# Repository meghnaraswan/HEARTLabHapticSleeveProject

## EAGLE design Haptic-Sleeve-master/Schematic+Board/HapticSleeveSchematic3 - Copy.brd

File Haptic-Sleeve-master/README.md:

# Haptic-Sleeve
Repository for the code used for the Haptic Sleeve Project!

Below is a brief description of the folders.

### CaseModels
Contains the 3D models that house the Haptic Sleeve PCB.

### ESP32 Code
Contains the Micropython code to run on the ESP32, along with Micropython firmware to flash (.bin file).

### Haptic Sleeve Testing Program
Contains the testing program and documentation for testing the Haptic Sleeve. The data extraction program (to convert log file data to CSV) also lives here.

### Learn To Write Code
Contains the code for the Learn To Write Software.

### Schematic+Board
Contains the schematic and board layout files for the Haptic Sleeve.

#### Activate venv
. venv/Scripts/activate

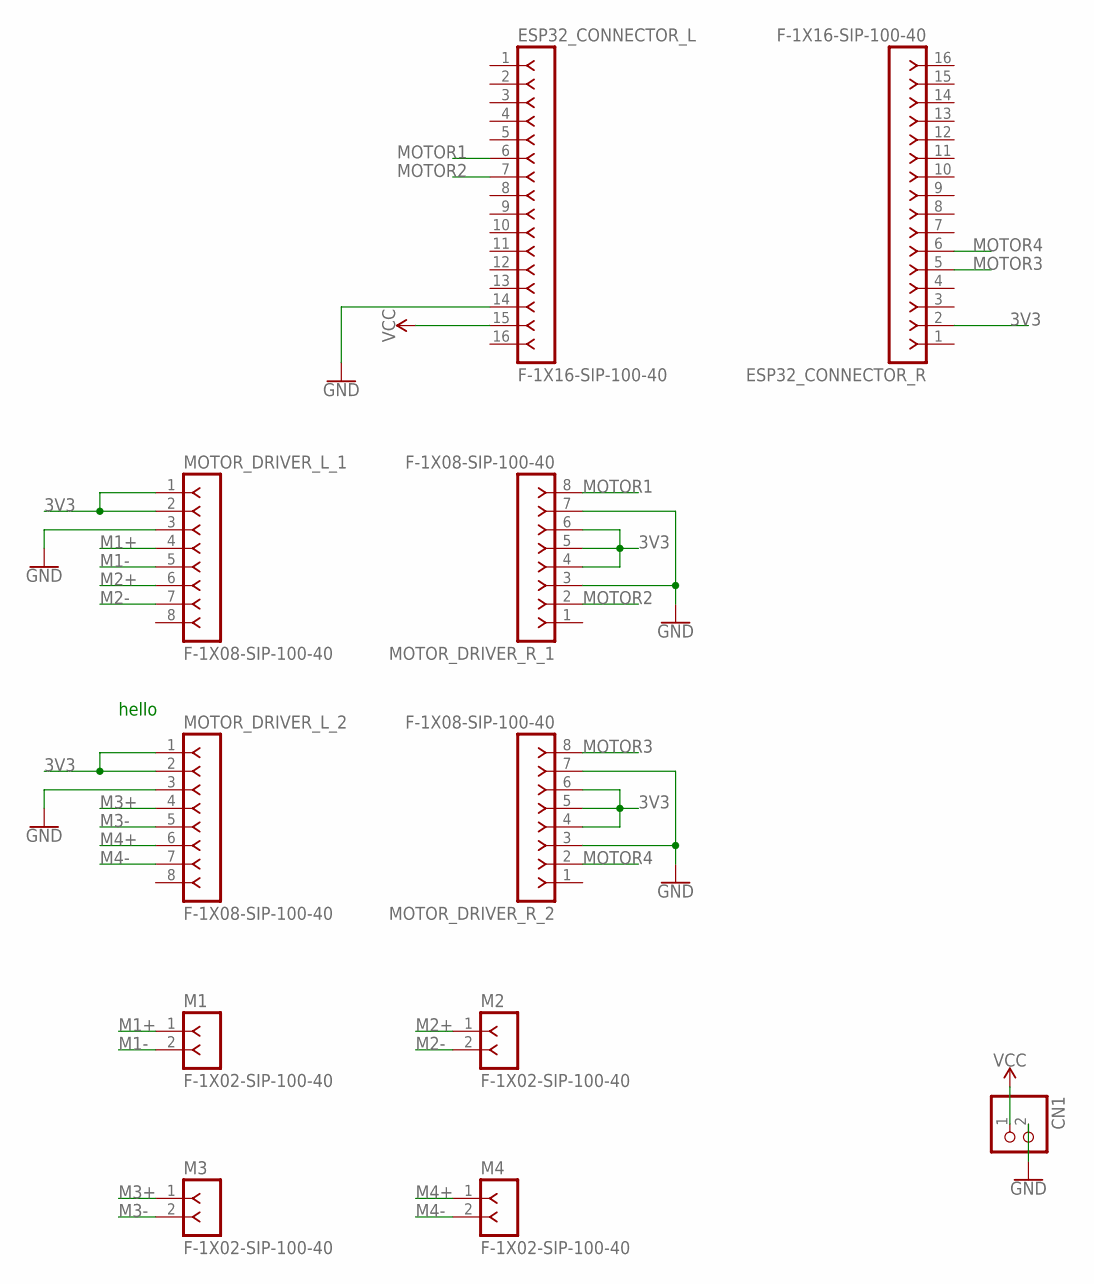
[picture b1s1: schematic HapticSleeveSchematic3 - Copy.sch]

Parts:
CN1: JST_2PIN-THM-RA; JST-PH-2-THM-RA
ESP32_CONNECTOR_L, ESP32_CONNECTOR_R: F-1X16-SIP-100-40; SIP-100-16-40
M1, M2, M3, M4: F-1X02-SIP-100-40; SIP-100-02-40
MOTOR_DRIVER_L_1, MOTOR_DRIVER_L_2: F-1X08-SIP-100-40; SIP-100-08-40
MOTOR_DRIVER_R_1, MOTOR_DRIVER_R_2: F-1X08-SIP-100-40; SIP-100-08-40

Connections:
3V3: ESP32_CONNECTOR_R.2, MOTOR_DRIVER_L_1.1, MOTOR_DRIVER_L_1.2, MOTOR_DRIVER_L_2.1, MOTOR_DRIVER_L_2.2, MOTOR_DRIVER_R_1.4, MOTOR_DRIVER_R_1.5, MOTOR_DRIVER_R_1.6, MOTOR_DRIVER_R_2.4, MOTOR_DRIVER_R_2.5, MOTOR_DRIVER_R_2.6
GND: CN1.2 (1), ESP32_CONNECTOR_L.14, MOTOR_DRIVER_L_1.3, MOTOR_DRIVER_L_2.3, MOTOR_DRIVER_R_1.3, MOTOR_DRIVER_R_1.7, MOTOR_DRIVER_R_2.3, MOTOR_DRIVER_R_2.7
M1+: M1.1, MOTOR_DRIVER_L_1.4
M1-: M1.2, MOTOR_DRIVER_L_1.5
M2+: M2.1, MOTOR_DRIVER_L_1.6
M2-: M2.2, MOTOR_DRIVER_L_1.7
M3+: M3.1, MOTOR_DRIVER_L_2.4
M3-: M3.2, MOTOR_DRIVER_L_2.5
M4+: M4.1, MOTOR_DRIVER_L_2.6
M4-: M4.2, MOTOR_DRIVER_L_2.7
MOTOR1: ESP32_CONNECTOR_L.6, MOTOR_DRIVER_R_1.8
MOTOR2: ESP32_CONNECTOR_L.7, MOTOR_DRIVER_R_1.2
MOTOR3: ESP32_CONNECTOR_R.5, MOTOR_DRIVER_R_2.8
MOTOR4: ESP32_CONNECTOR_R.6, MOTOR_DRIVER_R_2.2
VCC: CN1.1 (2), ESP32_CONNECTOR_L.15

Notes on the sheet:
hello

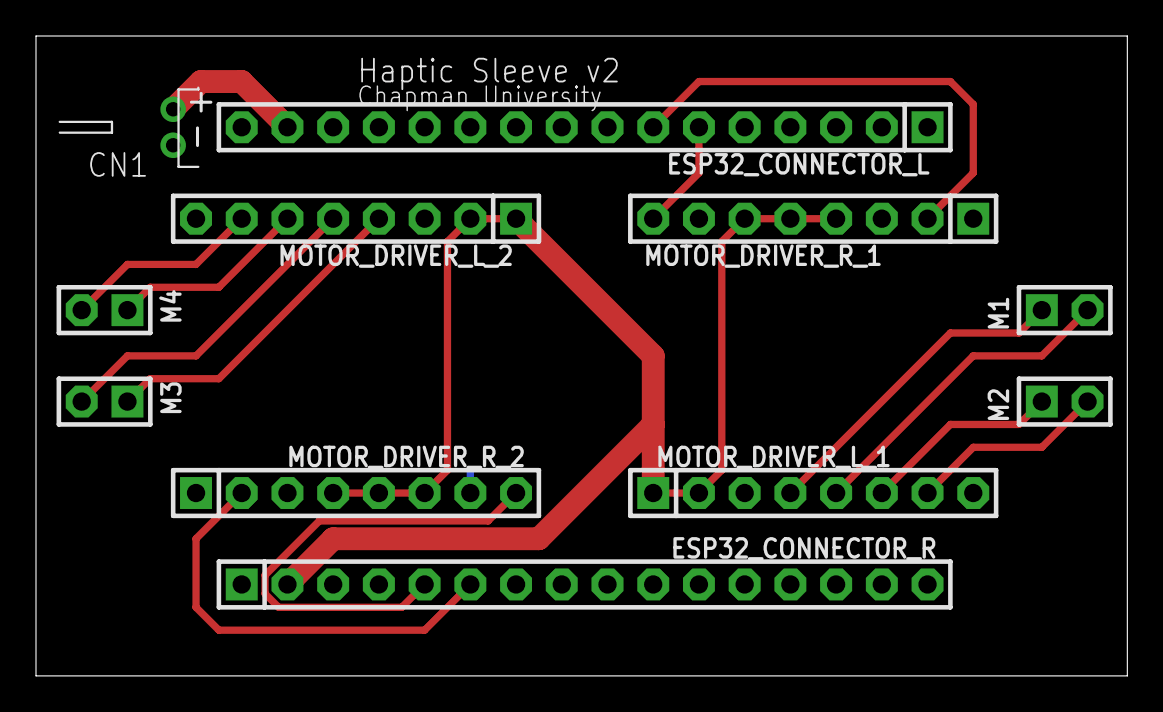
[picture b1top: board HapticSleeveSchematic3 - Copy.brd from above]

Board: 2 copper layers, 60.6 x 35.5 mm, 11 parts (0 on the bottom side), 15 nets.

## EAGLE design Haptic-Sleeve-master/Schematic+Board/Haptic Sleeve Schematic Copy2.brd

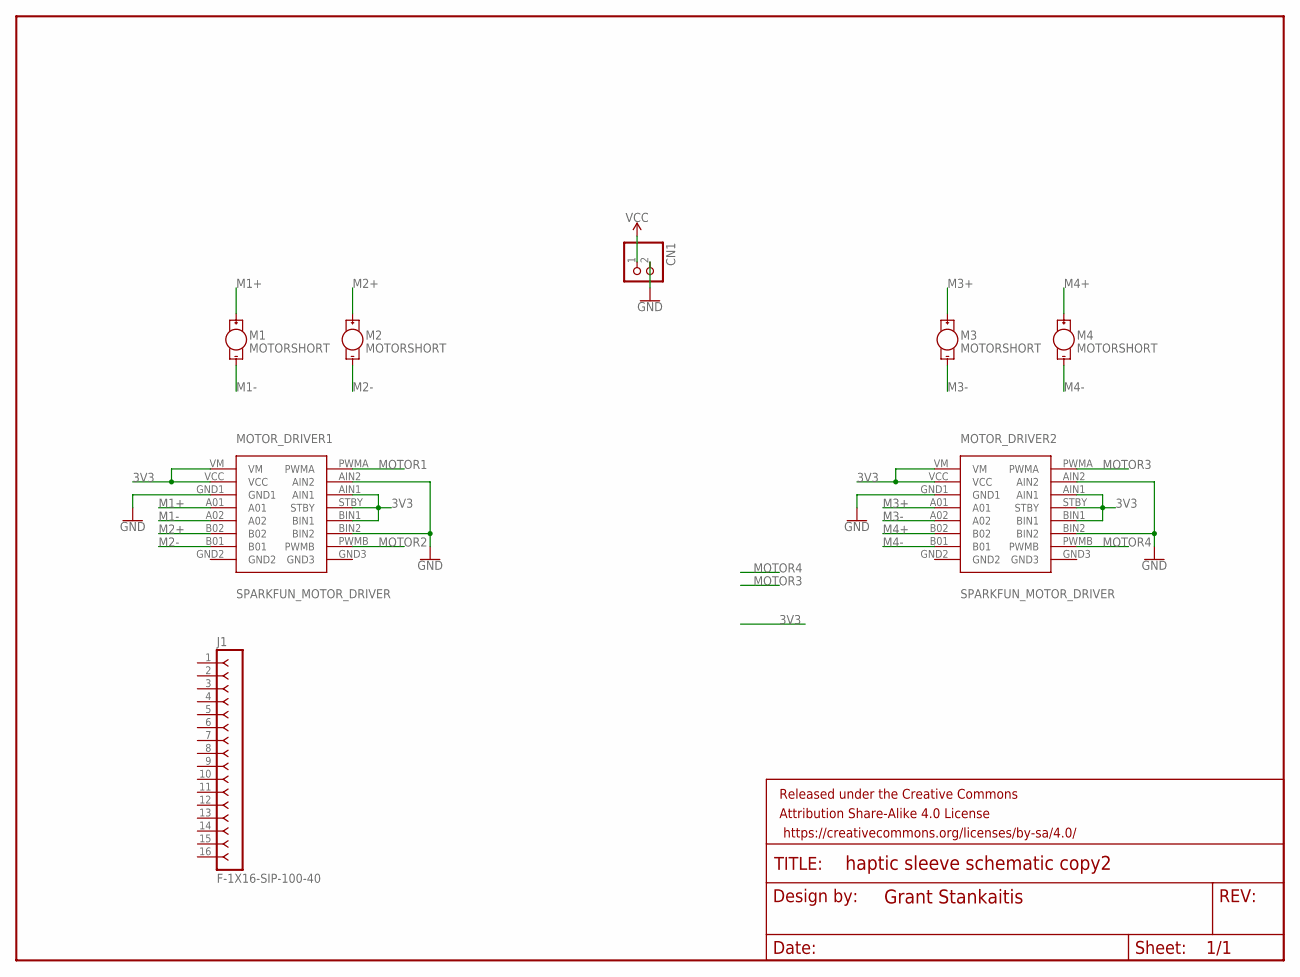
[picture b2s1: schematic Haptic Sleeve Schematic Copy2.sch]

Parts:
CN1: JST_2PIN-THM-RA; JST-PH-2-THM-RA
FRAME1: FRAME-LETTERNO_PACKAGE; DUMMY
J1: F-1X16-SIP-100-40; SIP-100-16-40
M1, M2, M3, M4: MOTORSHORT; VIBE-MOTOR-10MM-SMD
MOTOR_DRIVER1, MOTOR_DRIVER2: SPARKFUN_MOTOR_DRIVER

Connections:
3V3: MOTOR_DRIVER1.AIN1, MOTOR_DRIVER1.BIN1, MOTOR_DRIVER1.STBY, MOTOR_DRIVER1.VCC, MOTOR_DRIVER1.VM, MOTOR_DRIVER2.AIN1, MOTOR_DRIVER2.BIN1, MOTOR_DRIVER2.STBY, MOTOR_DRIVER2.VCC, MOTOR_DRIVER2.VM
GND: CN1.2 (1), MOTOR_DRIVER1.AIN2, MOTOR_DRIVER1.BIN2, MOTOR_DRIVER1.GND1, MOTOR_DRIVER2.AIN2, MOTOR_DRIVER2.BIN2, MOTOR_DRIVER2.GND1
M1+: M1.+, MOTOR_DRIVER1.A01
M1-: M1.-, MOTOR_DRIVER1.A02
M2+: M2.+, MOTOR_DRIVER1.B02
M2-: M2.-, MOTOR_DRIVER1.B01
M3+: M3.+, MOTOR_DRIVER2.A01
M3-: M3.-, MOTOR_DRIVER2.A02
M4+: M4.+, MOTOR_DRIVER2.B02
M4-: M4.-, MOTOR_DRIVER2.B01
MOTOR1: MOTOR_DRIVER1.PWMA
MOTOR2: MOTOR_DRIVER1.PWMB
MOTOR3: MOTOR_DRIVER2.PWMA
MOTOR4: MOTOR_DRIVER2.PWMB
VCC: CN1.1 (2)

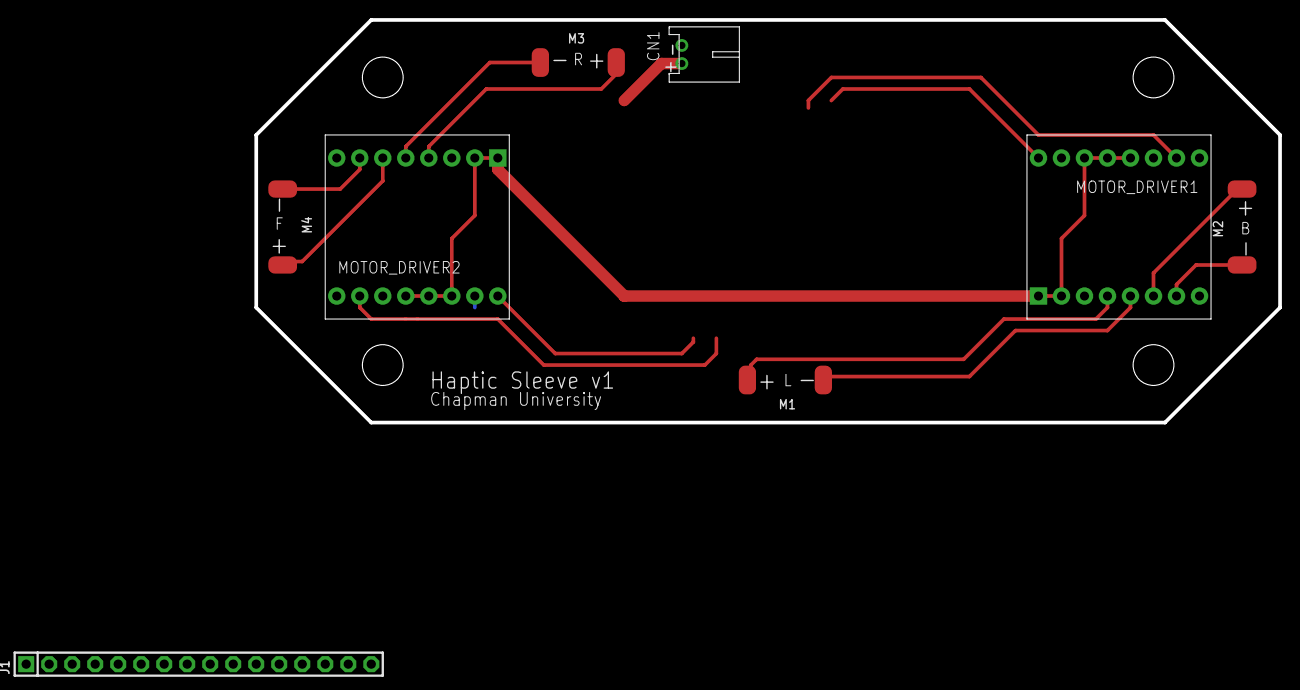
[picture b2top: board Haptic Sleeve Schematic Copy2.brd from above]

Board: 2 copper layers, 113.0 x 44.5 mm, 9 parts (0 on the bottom side), 10 nets.

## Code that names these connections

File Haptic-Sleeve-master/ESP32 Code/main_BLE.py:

import bluetooth
import time
import machine
from machine import Pin
from bleuart import BLEUART

# Forward motor pin B, PWMB, pin 4
# Left motor pin A, PWMA, pin 34
# Back motor pin B, PWMB, pin 35
# Right motor pin A, PWMA, pin 2
motor1 = machine.PWM(Pin(4))
motor2 = machine.PWM(Pin(32))
motor3 = machine.PWM(Pin(33))
motor4 = machine.PWM(Pin(2))

motor1.freq(1000)
motor2.freq(1000)
motor3.freq(1000)
motor4.freq(1000)

motor1.duty(0)
motor2.duty(0)
motor3.duty(0)
motor4.duty(0)

forward = 0
left = 0
back = 0
right = 0

def start_sleeve():
    ble = bluetooth.BLE()
    uart = BLEUART(ble)
 
    def set_PWM():
      # Read and decode data sent over BLE UART
      rx_payload = uart.read().decode().strip()
      
      # Split the formatted payload for direction and range
      # Assumes that sent messages are formatted properly & non-empty
      direction, range = rx_payload.split(',')
      direction = int(direction)
      range = int(range)
      
      # Range comes in 0, 1, 2, 3
      # Duty is 1/3 of the max, ie. 33.33%, 66.33%, 100%
      # Max for PWM is 1023, 341 is 1/3 *1023
      duty = int(range*341)
      
      # Assign duty based on direction
      if direction == 1:
        forward = duty
        left = 0
        back = 0
        right = 0
      elif direction == 2:
        forward = 0
        left = duty
        back = 0
        right = 0
      elif direction == 3:
        forward = 0
        left = 0
        back = duty
        right = 0
      elif direction == 4:
        forward = 0
        left = 0
        back = 0
        right = duty
      else: # Set all to 0
        forward = 0
        left = 0
        back = 0
        right = 0
      
      # Set duty
      motor1.duty(forward)
      motor2.duty(left)
      motor3.duty(back)
      motor4.duty(right)
    
    # Set callback for BLE event
    # Callbacks triggered immediately when new payload received
    uart.irq(handler = set_PWM)

    try:
      while True: # Infinite loop, sleep used as a placeholder
        time.sleep_ms(1)
    except KeyboardInterrupt:
      pass

    # Close the BLE UART connection
    uart.close()

if __name__ == "__main__":
    start_sleeve()


    

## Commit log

2021-08-05 adding HapticSleeve3.sch and HapticSleeve3.brd
2021-08-12 HapticSleeveSchematic3.brd has 4 motors on one side of board with more routing. HapticSleeveSchematic3 - Copy.brd has 2 motors on each side of the board with less routing
2021-08-17 made changes to HapticSleeveSchematic3 - Copy.brd by rerouting and adding silkscreen for ESP32 Connectors
2021-08-17 shortened PCB route

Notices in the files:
parts and their libraries:
SparkFun-Aesthetics: Licensing: Creative Commons ShareAlike 4.0 International - https://creativecommons.org/licenses/by-sa/4.0
con-headers-jp-1: Copyright (C) 2008, Bob Starr
SparkFun-Aesthetics: Released under the Creative Commons Attribution Share-Alike 4.0 License
